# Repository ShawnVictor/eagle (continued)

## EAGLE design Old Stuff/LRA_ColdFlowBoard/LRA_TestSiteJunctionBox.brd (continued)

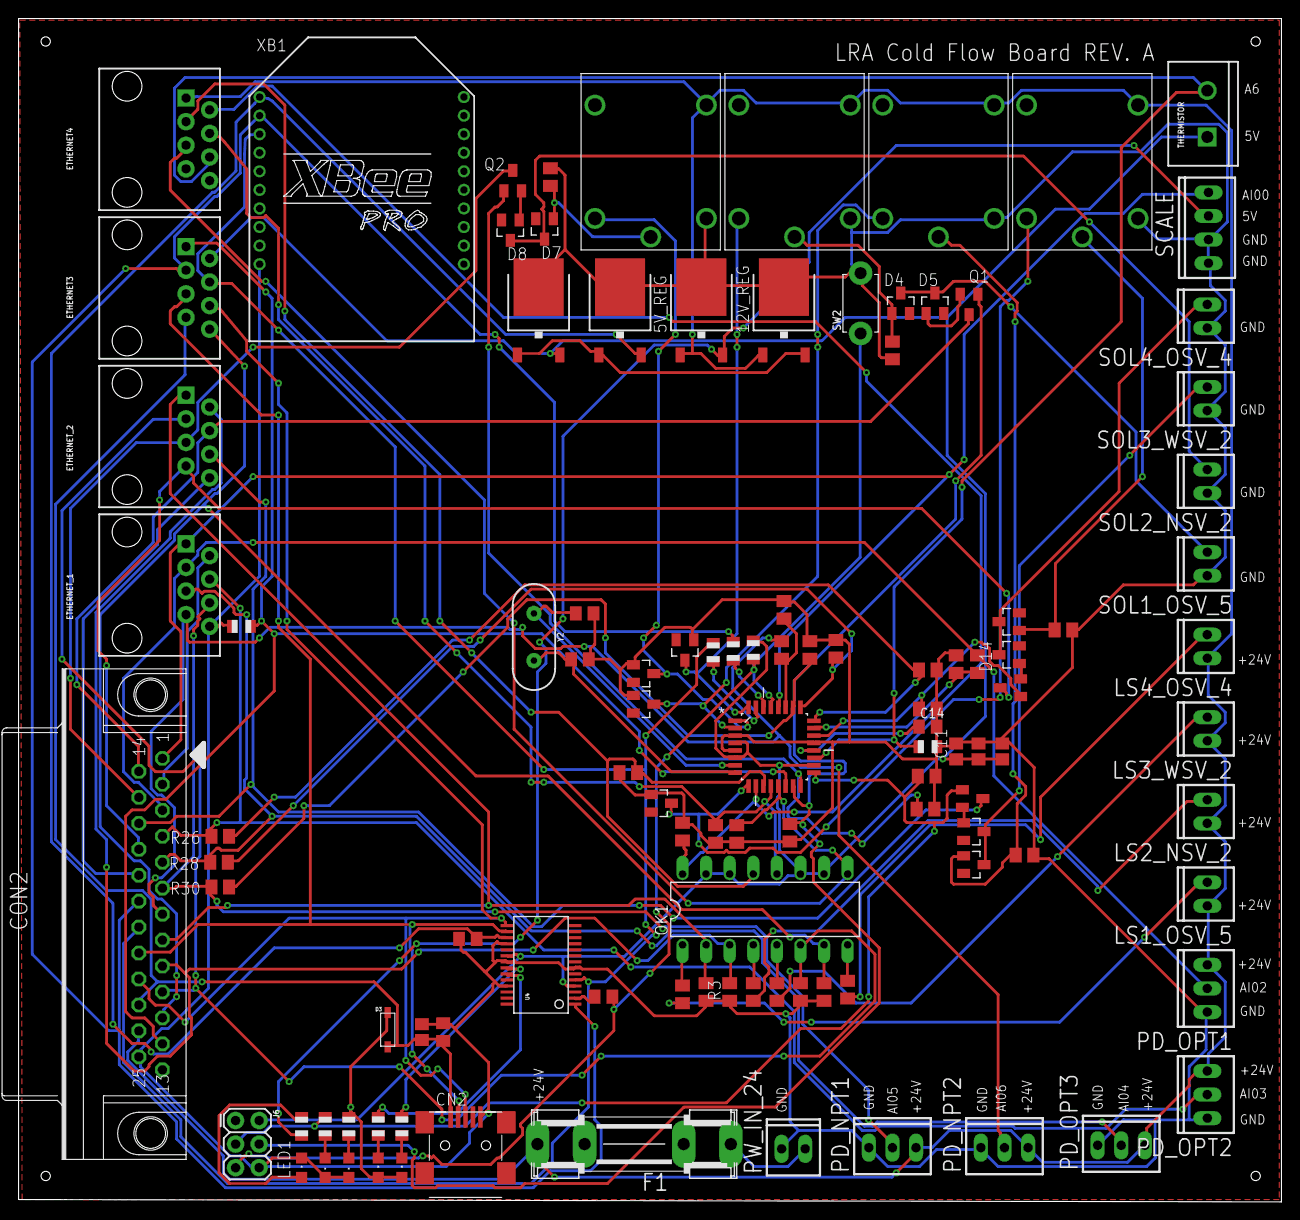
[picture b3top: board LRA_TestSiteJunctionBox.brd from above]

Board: 2 copper layers, 136.0 x 127.4 mm, 110 parts (0 on the bottom side), 81 nets.

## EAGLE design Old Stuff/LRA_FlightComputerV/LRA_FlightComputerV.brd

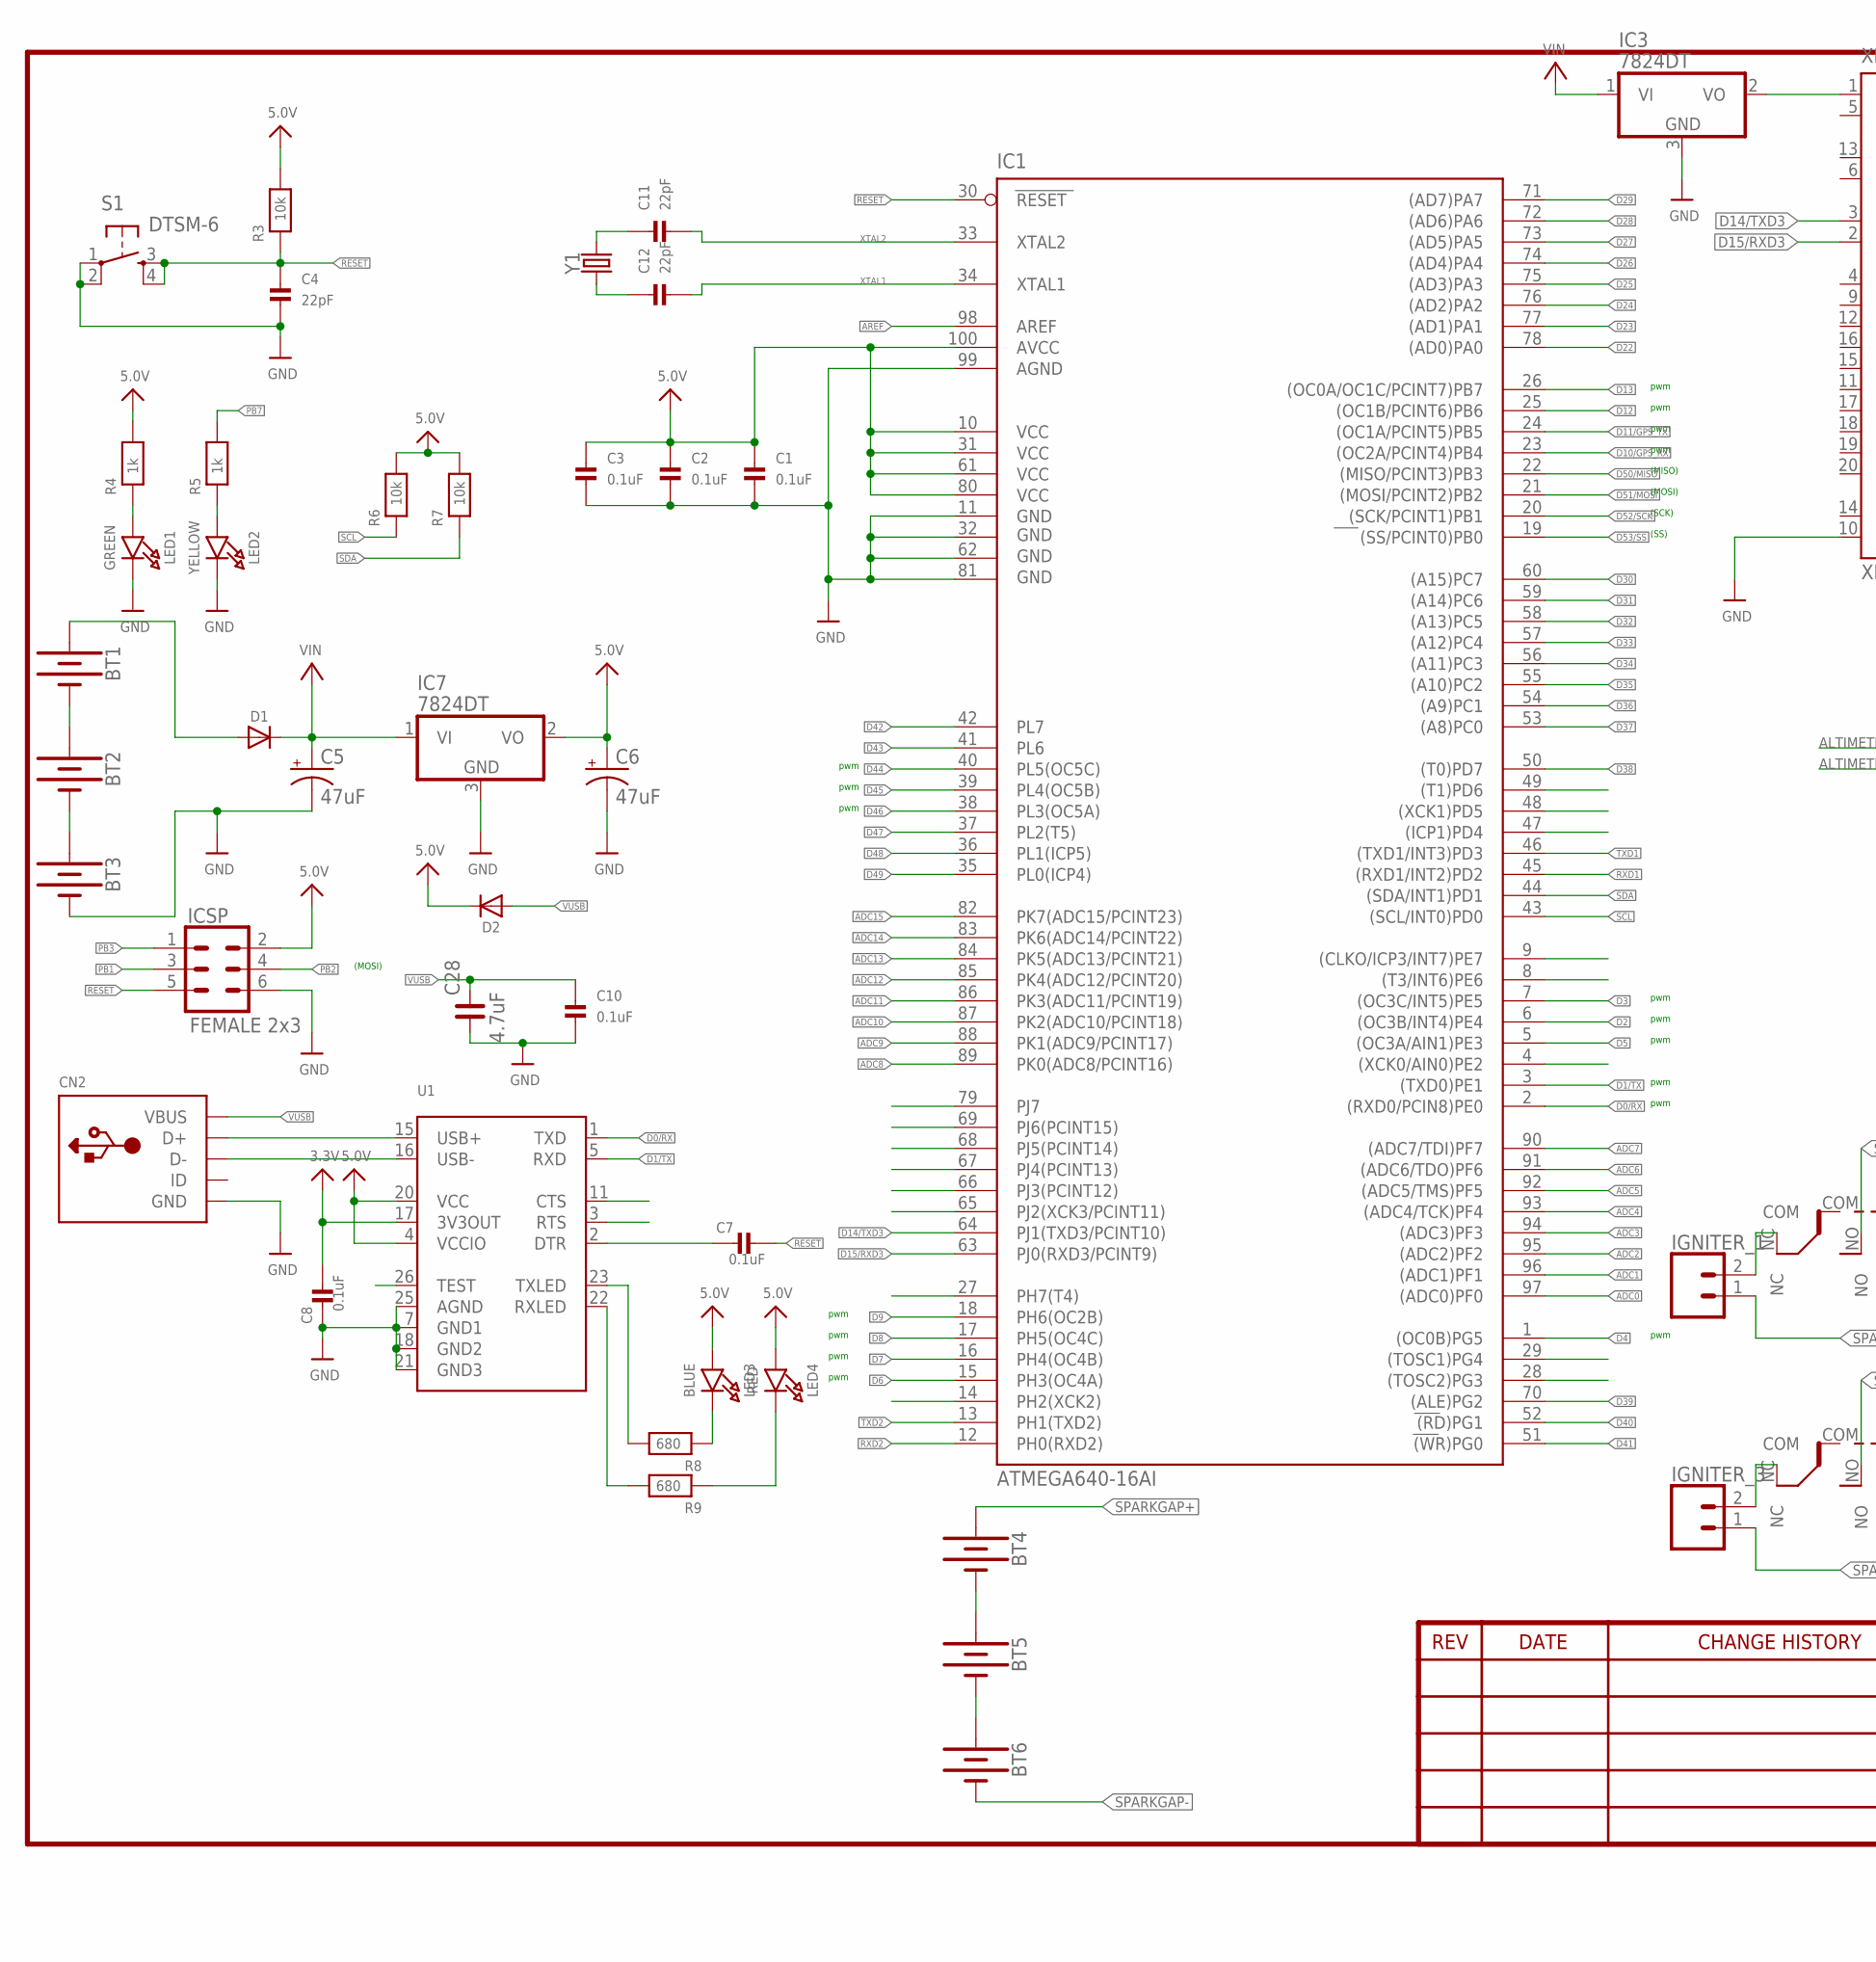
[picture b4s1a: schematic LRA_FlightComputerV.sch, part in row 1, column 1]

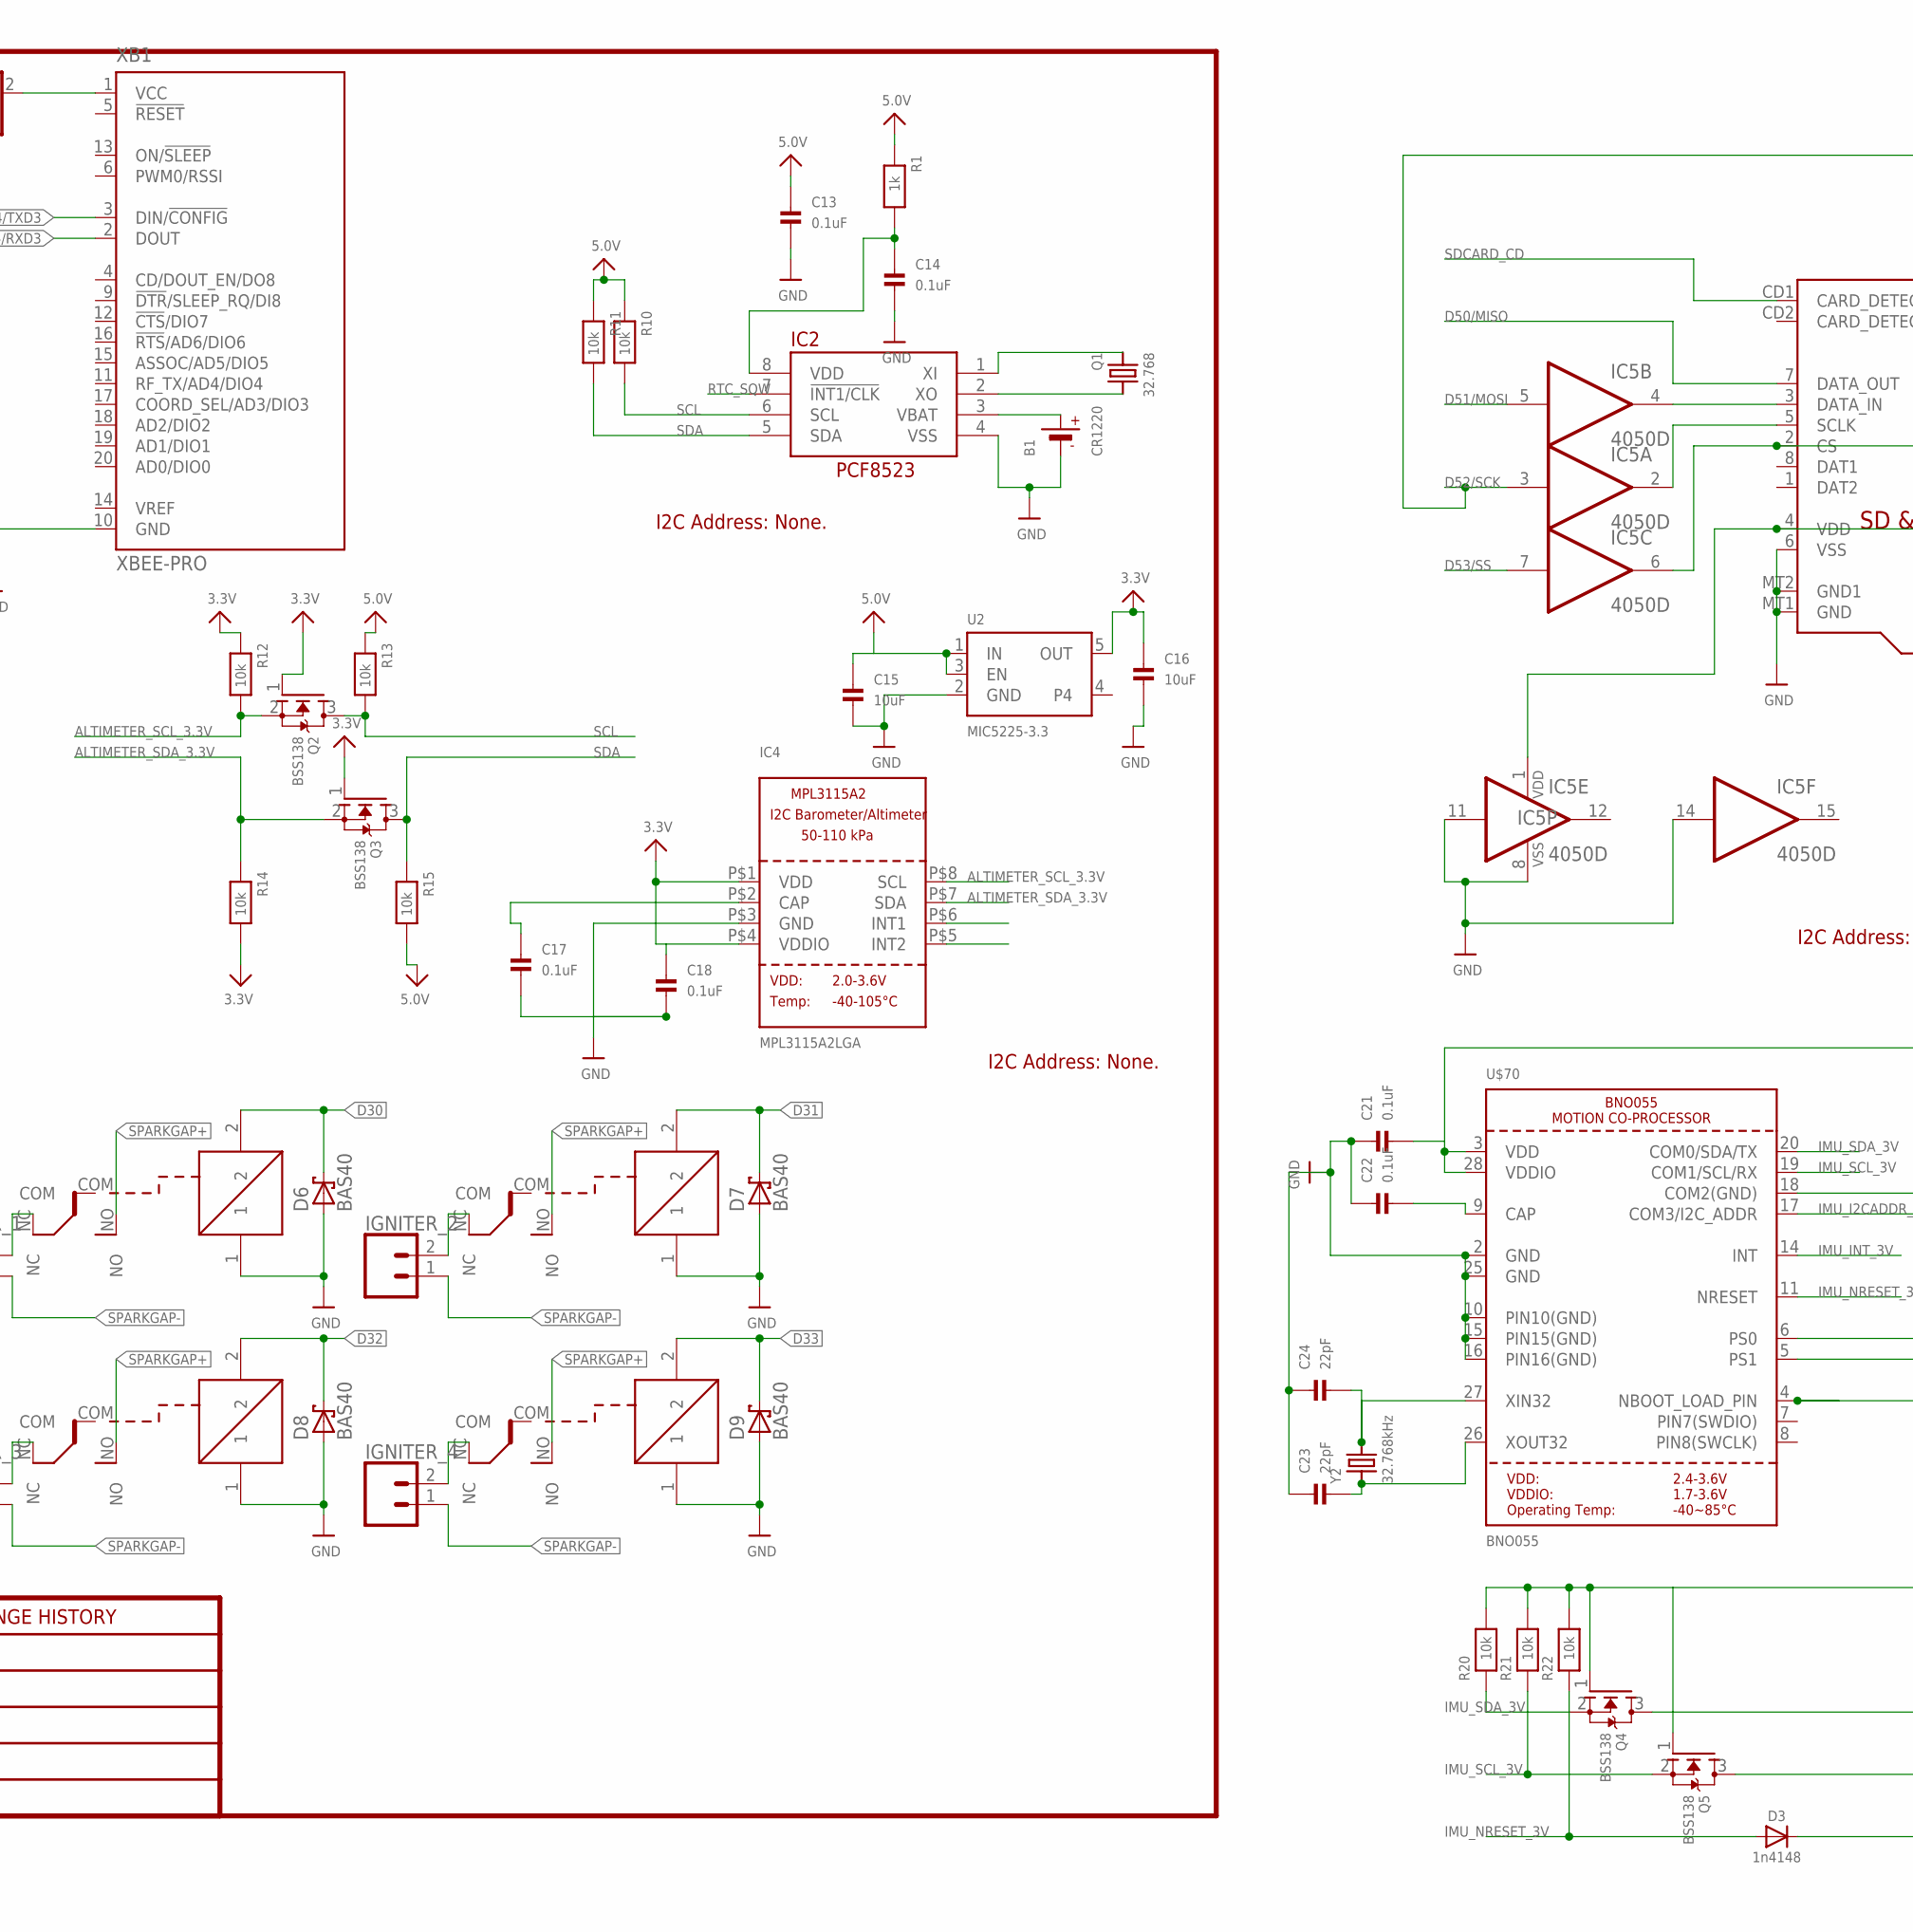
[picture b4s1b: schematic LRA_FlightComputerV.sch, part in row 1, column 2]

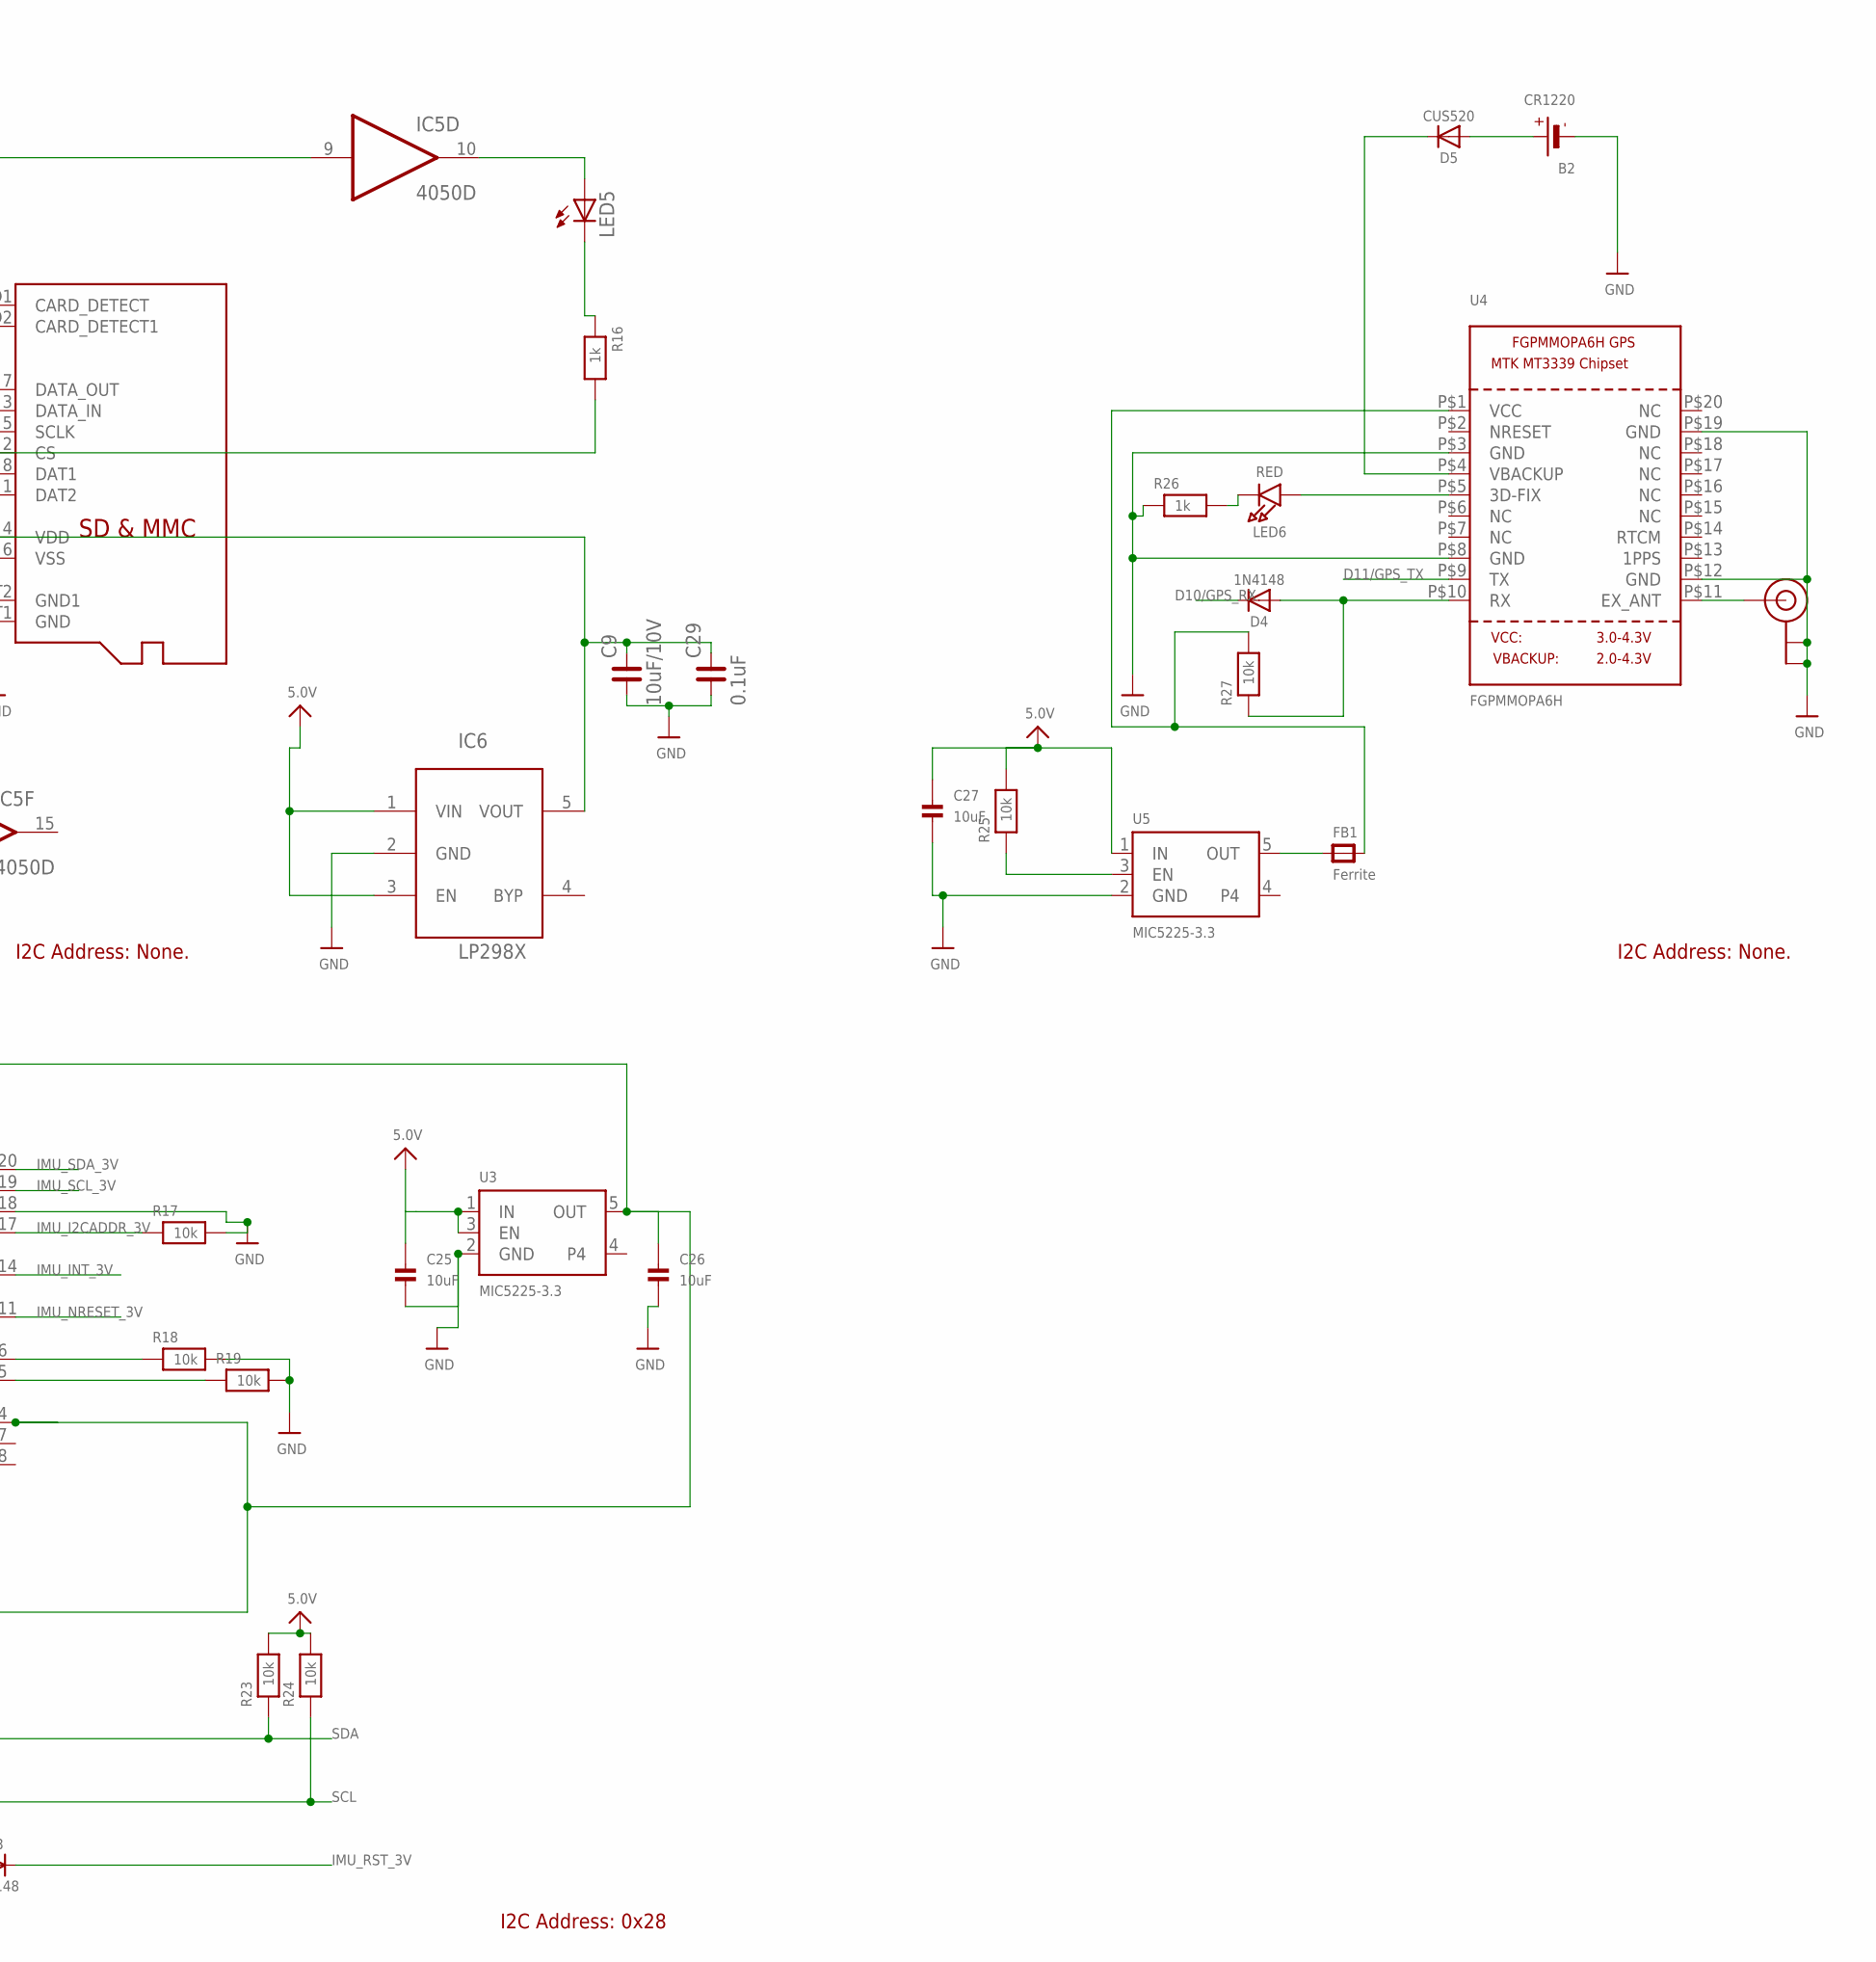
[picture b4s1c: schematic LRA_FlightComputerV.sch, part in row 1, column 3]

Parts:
B1, B2: CR1220
BT1, BT2, BT3, BT4, BT5, BT6: BATTERY-18650; BATTERY_18650-HOLDER
C1, C2, C3, C7, C8, C10, C13, C14, C17, C18, C21, C22: 0.1uF; 0805@1
C4, C11, C12, C23, C24: 22pF; 0805@1
C5, C6: 47uF; PANASONIC_D
C9: 10uF/10V; C0805
C15, C16, C25, C26, C27: 10uF; 0805@1
C28: 4.7uF; C0805
C29: 0.1uF; C0805
CN2: USBMINIB; USB-MINIB
D1, D2: DIODESOD-123; SOD-123
D3: 1n4148; SOD-323
D4: 1N4148; SOD-323
D5: CUS520; SOD-323
D6, D7, D8, D9: BAS40; SOT23
FB1: Ferrite; 0805-NO
IC1: ATMEGA640-16AI; TQFP100
IC2: RTC_PCF8523T; SOIC8_150MIL
IC3, IC7: 7824DT; TO252
IC4: MPL3115A2LGA; LGA8
IC5: 4050D; SO16
IC6: LP298XS; SOT23-5L
ICSP: FEMALE 2x3; 2X3
IGNITER_1, IGNITER_2, IGNITER_3, IGNITER_4: CONN_02; 1X02
LED1: GREEN; CHIPLED_0805
LED2: YELLOW; CHIPLED_0805
LED3: BLUE; CHIPLED_0805
LED4, LED6: RED; CHIPLED_0805
LED5: LEDCHIPLED_0805; CHIPLED_0805
Q1: 32.768; CRYSTAL_8X3.8
Q2, Q3, Q4, Q5: BSS138; SOT23-WIDE
R1, R4, R5, R16, R26: 1k; 0805@1
R3, R6, R7, R10, R11, R12, R13, R14, R15, R17, R18, R19, R20, R21, R22, R23, R24, R25, R27: 10k; 0805@1
R8, R9: 680; 0805@1
S1: DTSM-6
U1: FT232RLSSOP28; SSOP28DB
U2, U3, U5: MIC5225-3.3; SOT23-5
U4: FGPMMOPA6H
U$70: BNO055
U$78: U.FL
U$84, U$86, U$87, U$90: RW-SH
X1: MICROSD
XB1: XBEE-PRO
Y1: CRYSTALPTH-HC49US; HC49US
Y2: 32.768kHz; CRYSTAL_8X3.8

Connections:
3.3V: C8.2, C16.2, C18.2, IC4.P$1 (VDD), IC4.P$4 (VDDIO), Q2.1 (G), Q3.1 (G), R12.1, R14.2, U1.17 (3V3OUT), U2.5 (OUT)
5.0V: C1.1, C2.1, C3.1, C6.+, C13.2, C15.2, C25.2, C27.2, D2.C, IC1.10 (VCC), IC1.31 (VCC1), IC1.61 (VCC2), IC1.80 (VCC3), IC1.100 (AVCC), IC6.1 (VIN), IC6.3 (EN), IC7.2 (VO), ICSP.2, LED3.A, LED4.A, R1.1, R3.2, R4.2, R6.2, R7.2, R10.1, R11.1, R13.1, R15.2, R23.2, R24.2, R25.2, U1.4 (VCCIO), U1.20 (VCC), U2.1 (IN), U2.3 (EN), U3.1 (IN), U3.3 (EN), U5.1 (IN)
ADC0: IC1.97 ((ADC0)PF0)
ADC1: IC1.96 ((ADC1)PF1)
ADC2: IC1.95 ((ADC2)PF2)
ADC3: IC1.94 ((ADC3)PF3)
ADC4: IC1.93 ((ADC4/TCK)PF4)
ADC5: IC1.92 ((ADC5/TMS)PF5)
ADC6: IC1.91 ((ADC6/TDO)PF6)
ADC7: IC1.90 ((ADC7/TDI)PF7)
ADC8: IC1.89 (PK0(ADC8/PCINT16))
ADC9: IC1.88 (PK1(ADC9/PCINT17))
ADC10: IC1.87 (PK2(ADC10/PCINT18))
ADC11: IC1.86 (PK3(ADC11/PCINT19))
ADC12: IC1.85 (PK4(ADC12/PCINT20))
ADC13: IC1.84 (PK5(ADC13/PCINT21))
ADC14: IC1.83 (PK6(ADC14/PCINT22))
ADC15: IC1.82 (PK7(ADC15/PCINT23))
ALTIMETER_SCL_3.3V: IC4.P$8 (SCL), Q2.2 (S), R12.2
ALTIMETER_SDA_3.3V: IC4.P$7 (SDA), Q3.2 (S), R14.1
AREF: IC1.98 (AREF)
D0/RX: IC1.2 ((RXD0/PCIN8)PE0), U1.1 (TXD)
D1/TX: IC1.3 ((TXD0)PE1), U1.5 (RXD)
D2: IC1.6 ((OC3B/INT4)PE4)
D3: IC1.7 ((OC3C/INT5)PE5)
D4: IC1.1 ((OC0B)PG5)
D5: IC1.5 ((OC3A/AIN1)PE3)
D6: IC1.15 (PH3(OC4A))
D7: IC1.16 (PH4(OC4B))
D8: IC1.17 (PH5(OC4C))
D9: IC1.18 (PH6(OC2B))
D10/GPS_RX: D4.C, IC1.23 ((OC2A/PCINT4)PB4)
D11/GPS_TX: IC1.24 ((OC1A/PCINT5)PB5), U4.P$9 (TX)
D12: IC1.25 ((OC1B/PCINT6)PB6)
D13: IC1.26 ((OC0A/OC1C/PCINT7)PB7)
D14/TXD3: IC1.64 (PJ1(TXD3/PCINT10)), XB1.3 (DIN/!CONFIG)
D15/RXD3: IC1.63 (PJ0(RXD3/PCINT9)), XB1.2 (DOUT)
D22: IC1.78 ((AD0)PA0)
D23: IC1.77 ((AD1)PA1)
D24: IC1.76 ((AD2)PA2)
D25: IC1.75 ((AD3)PA3)
D26: IC1.74 ((AD4)PA4)
D27: IC1.73 ((AD5)PA5)
D28: IC1.72 ((AD6)PA6)
D29: IC1.71 ((AD7)PA7)
D30: D6.3 (C), IC1.60 ((A15)PC7), U$87.2
D31: D7.3 (C), IC1.59 ((A14)PC6), U$84.2
D32: D8.3 (C), IC1.58 ((A13)PC5), U$86.2
D33: D9.3 (C), IC1.57 ((A12)PC4), U$90.2
D34: IC1.56 ((A11)PC3)
D35: IC1.55 ((A10)PC2)
D36: IC1.54 ((A9)PC1)
D37: IC1.53 ((A8)PC0)
D38: IC1.50 ((T0)PD7)
D39: IC1.70 ((ALE)PG2)
D40: IC1.52 ((RD)PG1)
D41: IC1.51 ((WR)PG0)
D42: IC1.42 (PL7)
D43: IC1.41 (PL6)
D44: IC1.40 (PL5(OC5C))
D45: IC1.39 (PL4(OC5B))
D46: IC1.38 (PL3(OC5A))
D47: IC1.37 (PL2(T5))
D48: IC1.36 (PL1(ICP5))
D49: IC1.35 (PL0(ICP4))
D50/MISO: IC1.22 ((MISO/PCINT3)PB3), X1.7 (DATA_OUT)
D51/MOSI: IC1.21 ((MOSI/PCINT2)PB2), IC5.5 (I)
D52/SCK: IC1.20 ((SCK/PCINT1)PB1), IC5.3 (I), IC5.9 (I)
D53/SS: IC1.19 ((SS/PCINT0)PB0), IC5.7 (I)
GND: B1.-, B2.-, BT3.GND@1 (-), C1.2, C2.2, C3.2, C4.2, C5.-, C6.-, C8.1, C9.1, C10.1, C13.1, C14.1, C15.1, C16.1, C17.1, C18.1, C21.2, C22.2, C23.1, C24.1, C25.1, C26.1, C27.1, C28.1, C29.1, CN2.GND, D6.1 (A), D7.1 (A), D8.1 (A), D9.1 (A), IC1.11 (GND), IC1.32 (GND1), IC1.62 (GND2), IC1.81 (GND3), IC1.99 (AGND), IC2.4 (VSS), IC3.3 (GND), IC4.P$3 (GND), IC5.8 (VSS), IC5.11 (I), IC5.14 (I), IC6.2 (GND), IC7.3 (GND), ICSP.6, LED1.C, LED2.C, R17.2, R18.2, R19.2, R26.1, S1.1, S1.2, U1.7 (GND1), U1.18 (GND2), U1.21 (GND3), U1.25 (AGND), U2.2 (GND), U3.2 (GND), U4.P$3 (GND), U4.P$8 (GND), U4.P$12 (GND), U4.P$19 (GND), U5.2 (GND), U$70.2 (GND), U$70.10 (PIN10(GND)), U$70.15 (PIN15(GND)), U$70.16 (PIN16(GND)), U$70.18 (COM2(GND)), U$70.25 (GND), U$78.P$1 (GND), U$78.P$2 (GND), U$84.1, U$86.1, U$87.1, U$90.1, X1.6 (VSS), X1.MT1 (GND), X1.MT2 (GND1), XB1.10 (GND)
IMU_I2CADDR_3V: R17.1, U$70.17 (COM3/I2C_ADDR)
IMU_INT_3V: U$70.14 (INT)
IMU_NRESET_3V: D3.A, R22.1, U$70.11 (NRESET)
IMU_RST_3V: D3.C
IMU_SCL_3V: Q5.2 (S), R21.1, U$70.19 (COM1/SCL/RX)
IMU_SDA_3V: Q4.2 (S), R20.1, U$70.20 (COM0/SDA/TX)
unnamed: BT2.GND@1 (-), BT3.PWR@1 (+)
unnamed: CN2.D+, U1.15 (USB+)
unnamed: CN2.D-, U1.16 (USB-)
unnamed: LED1.A, R4.1
unnamed: LED2.A, R5.1
unnamed: LED3.C, R8.1
unnamed: R9.2, U1.22 (RXLED)
unnamed: R8.2, U1.23 (TXLED)
unnamed: LED4.C, R9.1
unnamed: C11.1, Y1.2
unnamed: C7.1, U1.2 (DTR)
unnamed: C12.1, Y1.1
unnamed: C14.2, IC2.8 (VDD), R1.2
unnamed: IC5.4 (O), X1.3 (DATA_IN)
unnamed: C17.2, IC4.P$2 (CAP)
unnamed: IC5.2 (O), X1.5 (SCLK)
unnamed: IC2.1 (XI), Q1.P$1 (1)
unnamed: IC2.2 (XO), Q1.P$4 (2)
unnamed: B1.+$1 (+), B1.+$2 (+), IC2.3 (VBAT)
unnamed: IC5.6 (O), R16.2, X1.2 (CS)
unnamed: LED5.C, R16.1
unnamed: IC5.10 (O), LED5.A
unnamed: C24.2, U$70.27 (XIN32), Y2.P$4 (2)
unnamed: C22.1, U$70.9 (CAP)
unnamed: C23.2, U$70.26 (XOUT32), Y2.P$1 (1)
unnamed: R18.1, U$70.6 (PS0)
unnamed: R19.1, U$70.5 (PS1)
unnamed: R25.1, U5.3 (EN)
unnamed: LED6.C, R26.2
unnamed: FB1.2, R27.2, U4.P$1 (VCC)
unnamed: U4.P$11 (EX_ANT), U$78.P$3 (SIGNAL)
unnamed: D5.C, U4.P$4 (VBACKUP)
unnamed: B2.+$1 (+), B2.+$2 (+), D5.A
unnamed: D4.A, R27.1, U4.P$10 (RX)
unnamed: LED6.A, U4.P$5 (3D-FIX)
unnamed: BT1.GND@1 (-), BT2.PWR@1 (+)
unnamed: BT4.GND@1 (-), BT5.PWR@1 (+)
unnamed: BT1.PWR@1 (+), D1.A
unnamed: BT5.GND@1 (-), BT6.PWR@1 (+)
unnamed: IGNITER_1.2, U$87.NC
unnamed: IC3.2 (VO), XB1.1 (VCC)
unnamed: IGNITER_2.2, U$84.NC
unnamed: IGNITER_3.2, U$86.NC
unnamed: IGNITER_4.2, U$90.NC
OUT: C21.1, C26.2, FB1.1, Q4.1 (G), Q5.1 (G), R20.2, R21.2, R22.2, U3.5 (OUT), U5.5 (OUT), U$70.3 (VDD), U$70.4 (NBOOT_LOAD_PIN), U$70.28 (VDDIO)
PB1: ICSP.3
PB2: ICSP.4
PB3: ICSP.1
PB7: R5.2
RESET: C4.1, C7.2, IC1.30 (RESET), ICSP.5, R3.1, S1.3, S1.4
RTC_SQW: IC2.7 (!INT1/CLK)
RXD1: IC1.45 ((RXD1/INT2)PD2)
RXD2: IC1.12 (PH0(RXD2))
SCL: IC1.43 ((SCL/INT0)PD0), IC2.6 (SCL), Q2.3 (D), Q5.3 (D), R6.1, R10.2, R13.2, R24.1
SDA: IC1.44 ((SDA/INT1)PD1), IC2.5 (SDA), Q3.3 (D), Q4.3 (D), R7.1, R11.2, R15.1, R23.1
SDCARD_CD: X1.CD1 (CARD_DETECT)
SPARKGAP+: BT4.PWR@1 (+), U$84.NO, U$86.NO, U$87.NO, U$90.NO
SPARKGAP-: BT6.GND@1 (-), IGNITER_1.1, IGNITER_2.1, IGNITER_3.1, IGNITER_4.1
TXD1: IC1.46 ((TXD1/INT3)PD3)
TXD2: IC1.13 (PH1(TXD2))
VDD: C9.2, C29.2, IC5.1 (VDD), IC6.5 (VOUT), X1.4 (VDD)
VIN: C5.+, D1.C, IC3.1 (VI), IC7.1 (VI)
VUSB: C10.2, C28.2, CN2.VBUS, D2.A
XTAL1: C12.2, IC1.34 (XTAL1)
XTAL2: C11.2, IC1.33 (XTAL2)

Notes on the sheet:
pwm
(SS)
(SCK)
(MOSI)
(MISO)
I2C Address: None.
I2C Address: 0x28

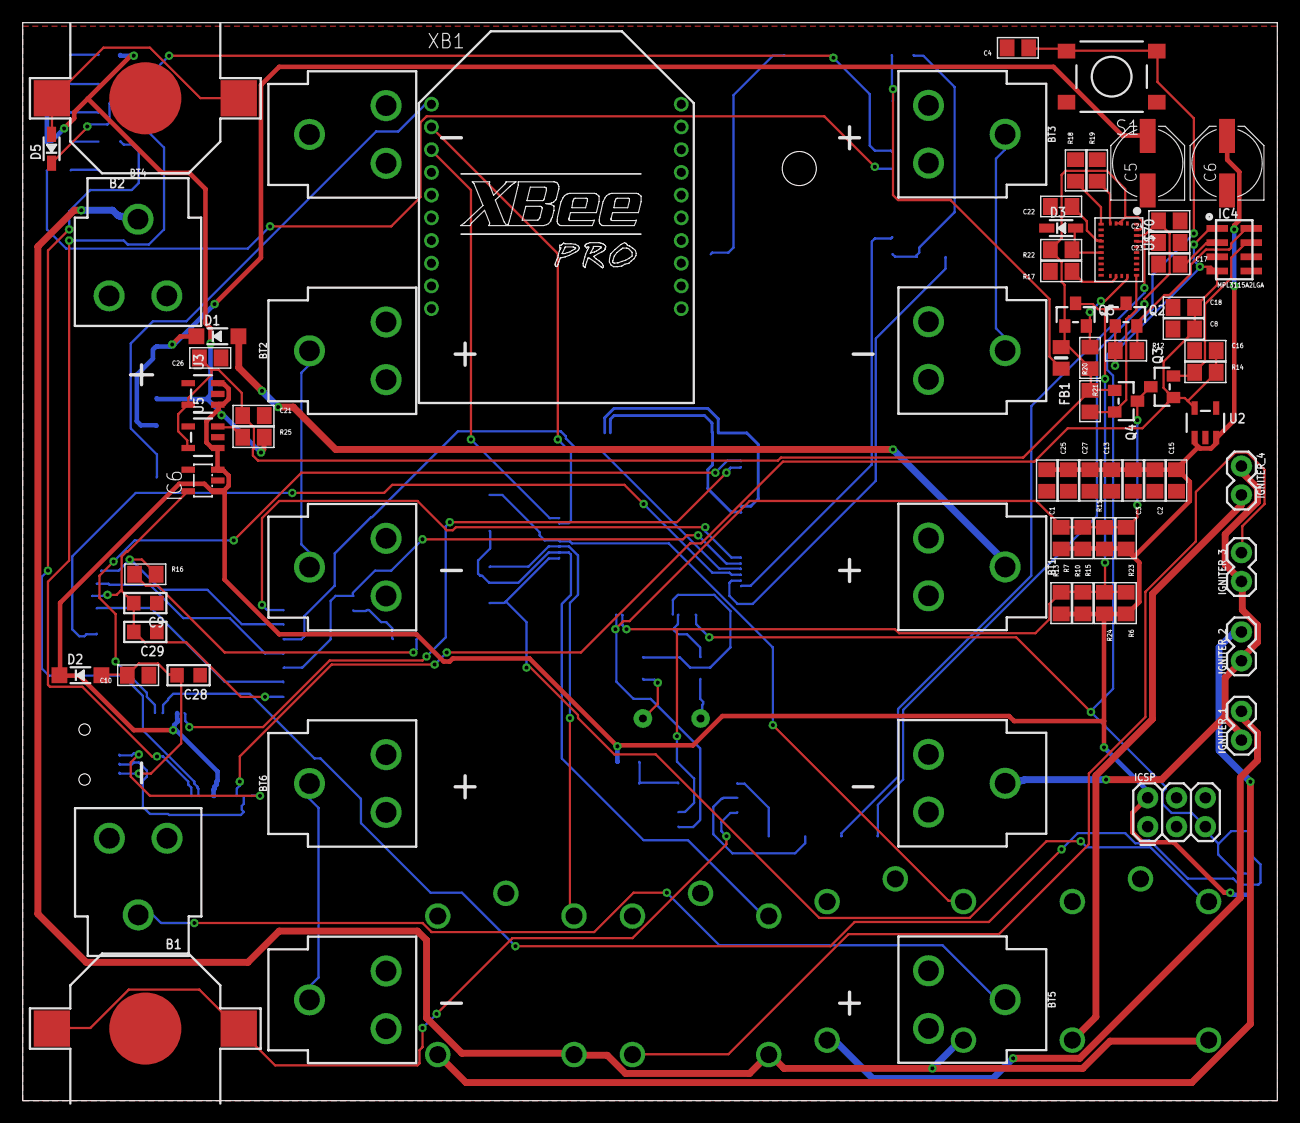
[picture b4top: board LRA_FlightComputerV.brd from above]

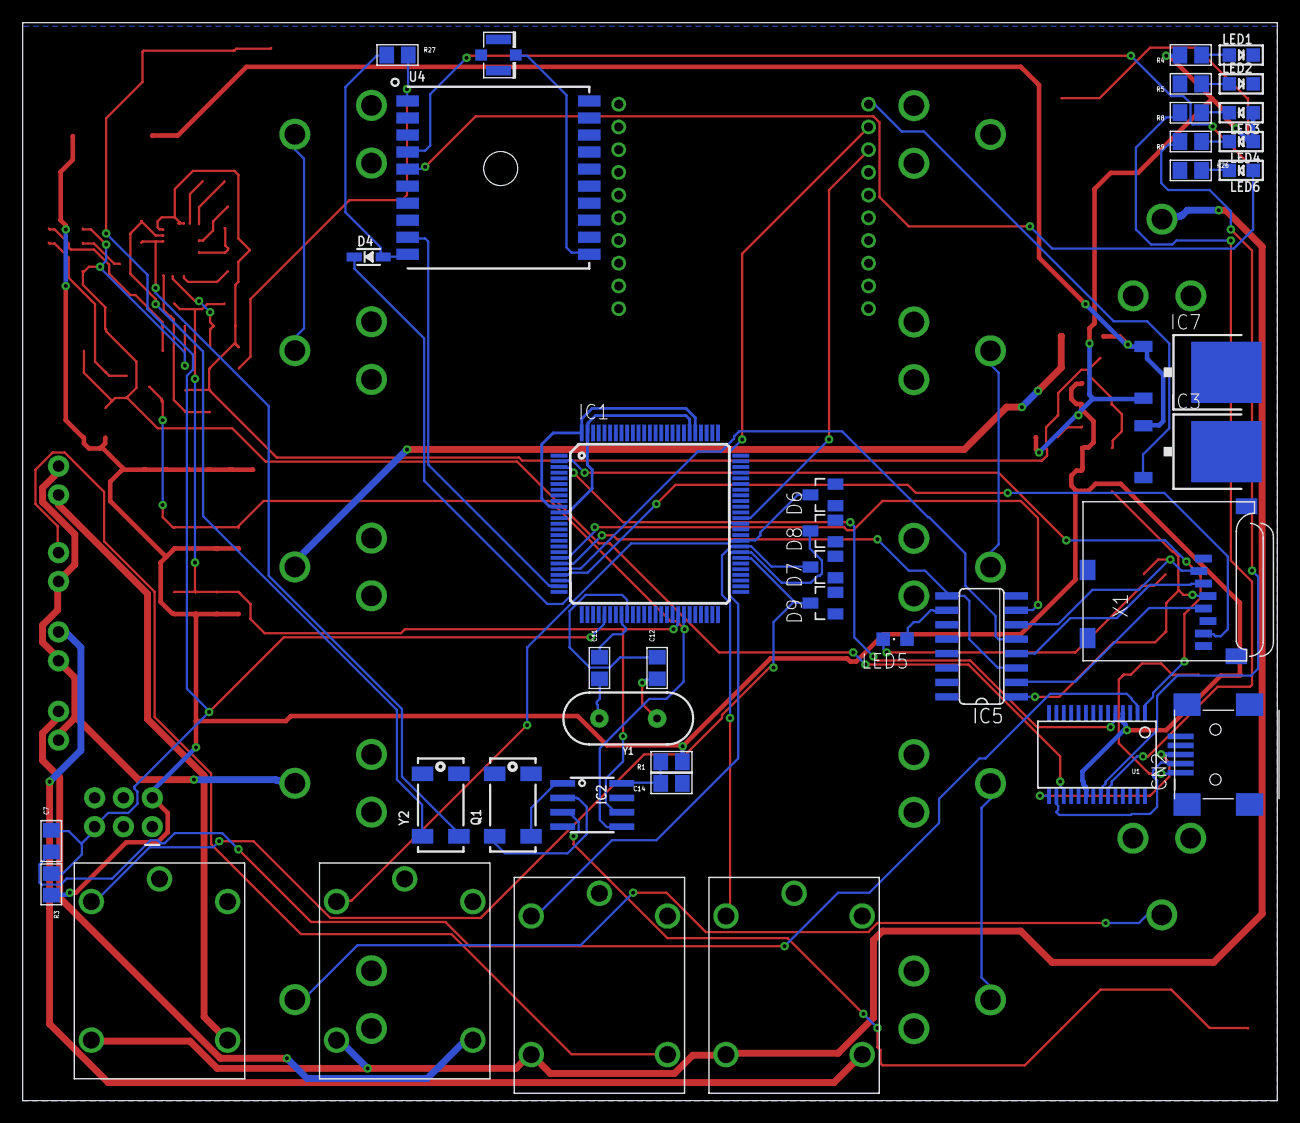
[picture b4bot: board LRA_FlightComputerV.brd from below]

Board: 2 copper layers, 110.5 x 94.9 mm, 111 parts (40 on the bottom side), 78 nets.
